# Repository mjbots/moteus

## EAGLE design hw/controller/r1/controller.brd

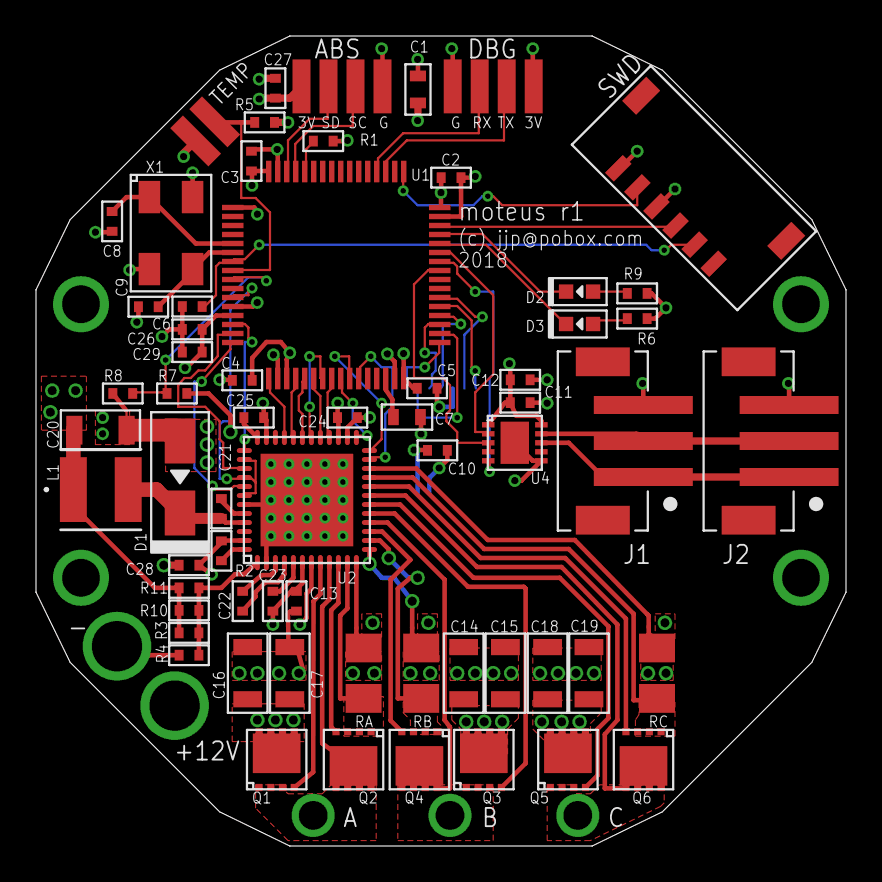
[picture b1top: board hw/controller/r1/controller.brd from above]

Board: 4 copper layers, 45.0 x 45.0 mm, 77 parts (1 on the bottom side), 68 nets.

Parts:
A: PAD; 18AWG_PAD
ABS: PAD4; PAD15_4
B: PAD; 18AWG_PAD
C: PAD; 18AWG_PAD
C1, C7: 4.7uF; C0603
C2, C3, C4, C5, C6, C10, C11, C13, C21, C22, C26: 0.1uF 50V; C0402
C8, C9: 10pF; C0402
C12, C23, C24, C25, C27, C28, C29: 1uF 35V; C0402
C14, C15, C16, C17, C18, C19, C20: 15uF; C1206
D1: MF-DIO-SMA-B140; SMA
D2, D3: MF-LED-0603-RED; LED0603
DBG: PAD4; PAD15_4
J1, J2: JST-PH3SMT_VERT; JST_B3B_PH-SM4-TB(LF)(SN)
L1: SRN4018-220M; IND_BOURNS_SRN4018
Q1, Q2, Q3, Q4, Q5, Q6: TPN1R603PL; TSON_ADVANCE_8
R1, R6, R9: 220; R0402
R2, R3, R7, R10, R11: 100k 1%; R0402
R4, R5, R8: 10k 1%; R0402
RA: 1mOhm 1% 2W; M1206
RB: 1mOhm 1% 2W; M1206
RC: 1mOhm 1% 2W; M1206
SH1, SH2, SH3: SHORTT5; SHORT_TOP-50
SH4: SHORTBIG; SHORT_TOP-BIG
SWD: JST-ZH6; JST_S6B-ZR-SM4A-TF(LF)(SN)
TEMP: PAD2; PAD15_2
U1: STM32F4R_64PIN; LQFP64
U2: DRV8323RS; PVQFN-N48
U3: AS5147; TSSOP14
U4: MAX13431E; TDFN10
U$1, U$2, U$3, U$4: MOUNTM2; M2MOUNT
V+: PAD12AWG_PAD; 12AWG_PAD
V-: PAD12AWG_PAD; 12AWG_PAD
X1: 8.0MHz; ABM3B

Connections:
+3V3: ABS.1, C1.P$1, C2.P$1, C3.P$1, C4.P$1, C5.P$1, C10.P$1, C11.P$1, C12.P$1, C20.P$1, C24.P$2, C26.P$1, C27.P$1, C29.P$1, DBG.1, L1.1, R3.P$1, R6.P$1, R9.P$1, R10.P$1, R11.P$1, SWD.6, TEMP.1, U1.1, U1.13, U1.19, U1.32, U1.48, U1.64, U2.26, U3.12, U4.1, U4.10
AS5047_A: U1.37, U3.7
AS5047_B: U1.38, U3.6
AS5047_CS: U1.33, U3.1
AS5047_MISO: U1.35, U3.3
AS5047_MOSI: U1.36, U3.4
AS5047_SCK: U1.34, U3.2
CUR1: U1.25, U2.25
CUR2: U1.26, U2.24
CUR3: U1.27, U2.23
DEBUG_RX: DBG.3, U1.52
DEBUG_TX: DBG.2, U1.51
DRV8323_CS: U1.20, U2.32
DRV8323_MISO: U1.22, U2.29
DRV8323_MOSI: U1.23, U2.30
DRV8323_SCLK: U1.21, U2.31
GHA: Q1.4, U2.8
GHB: Q3.4, U2.17
GHC: Q5.4, U2.18
GLA: Q2.4, U2.10
GLB: Q4.4, U2.15
GLC: Q6.4, U2.20
GND: ABS.4, C1.P$2, C2.P$2, C3.P$2, C4.P$2, C5.P$2, C6.P$2, C7.P$2, C8.P$2, C9.P$2, C10.P$2, C11.P$2, C12.P$2, C20.P$2, C24.P$1, C25.P$1, C26.P$2, C27.P$2, C29.P$2, DBG.4, J1.3, J2.3, R1.P$1, R5.P$2, R8.P$1, SH4.2, SWD.4, U1.12, U1.18, U1.31, U1.47, U1.63, U2.27, U2.35, U3.5, U3.13, U4.6, U4.PAD, X1.2, X1.4
I2C_ABS_SCL: ABS.3, U1.61
I2C_ABS_SDA: ABS.2, U1.62
LED1: D3.CATHODE, U1.44
LED2: D2.CATHODE, U1.45
MOTOR1: U1.14, U2.37
MOTOR2: U1.15, U2.39
MOTOR3: U1.16, U2.41
MOTOR_ENABLE: U1.17, U2.33
MOTOR_FAULT: U1.24, U2.28
MOTOR_HIZ: U1.11, U2.38, U2.40, U2.42
unnamed: R2.P$1, U2.48
unnamed: SWD.5, U1.49
unnamed: SWD.3, U1.46
unnamed: R3.P$2, R4.P$1, R10.P$2, R11.P$2, U2.1
unnamed: J1.2, J2.2, U4.9
unnamed: C22.P$2, U2.3
unnamed: C21.P$2, D1.CATHODE, L1.2, U2.45
unnamed: C21.P$1, U2.44
unnamed: C22.P$1, U2.4
unnamed: C23.P$2, U2.5
unnamed: J1.1, J2.1, U4.8
unnamed: C25.P$2, U2.36
unnamed: D3.ANODE, R6.P$2
unnamed: D2.ANODE, R9.P$2
unnamed: C7.P$1, U1.30
unnamed: C6.P$1, SWD.2, U1.7
unnamed: R1.P$2, U1.60
unnamed: C8.P$1, U1.5, X1.1
unnamed: C9.P$1, U1.6, X1.3
RS485_DIR: U1.41, U4.3, U4.4
RS485_RX: U1.43, U4.2
RS485_TX: U1.42, U4.5
SHA: A.1, Q1.1, Q1.2, Q1.3, Q2.5, Q2.6, Q2.7, Q2.8, Q2.PAD, U2.9
SHB: B.1, Q3.1, Q3.2, Q3.3, Q4.5, Q4.6, Q4.7, Q4.8, Q4.PAD, U2.16
SHC: C.1, Q5.1, Q5.2, Q5.3, Q6.5, Q6.6, Q6.7, Q6.8, Q6.PAD, U2.19
SNA: SH1.1, U2.12
SNB: SH2.1, U2.13
SNC: SH3.1, U2.22
SPA: Q2.1, Q2.2, Q2.3, RA.2, U2.11
SPB: Q4.1, Q4.2, Q4.3, RB.2, U2.14
SPC: Q6.1, Q6.2, Q6.3, RC.2, U2.21
V+: C13.P$1, C14.P$1, C15.P$1, C16.P$1, C17.P$1, C18.P$1, C19.P$1, C23.P$1, C28.P$1, Q1.5, Q1.6, Q1.7, Q1.8, Q1.PAD, Q3.5, Q3.6, Q3.7, Q3.8, Q3.PAD, Q5.5, Q5.6, Q5.7, Q5.8, Q5.PAD, R2.P$2, R7.P$2, U2.6, U2.7, U2.47, V+.1
V-: C13.P$2, C14.P$2, C15.P$2, C16.P$2, C17.P$2, C18.P$2, C19.P$2, C28.P$2, D1.ANODE, R4.P$2, RA.1, RB.1, RC.1, SH1.2, SH2.2, SH3.2, SH4.1, U2.2, U2.43, U2.P1, U2.P2, U2.P3, U2.P4, U2.P5, U2.P6, U2.P7, U2.P8, U2.P9, U2.P10, U2.P11, U2.P12, U2.P13, U2.P14, U2.P15, U2.P16, U2.P17, U2.P18, U2.P19, U2.P20, U2.P21, U2.P22, U2.P23, U2.P24, U2.P25, U2.PAD, V-.1
VBAT_SENSE: R7.P$1, R8.P$2, U1.9
VTEMP: R5.P$1, TEMP.2, U1.8

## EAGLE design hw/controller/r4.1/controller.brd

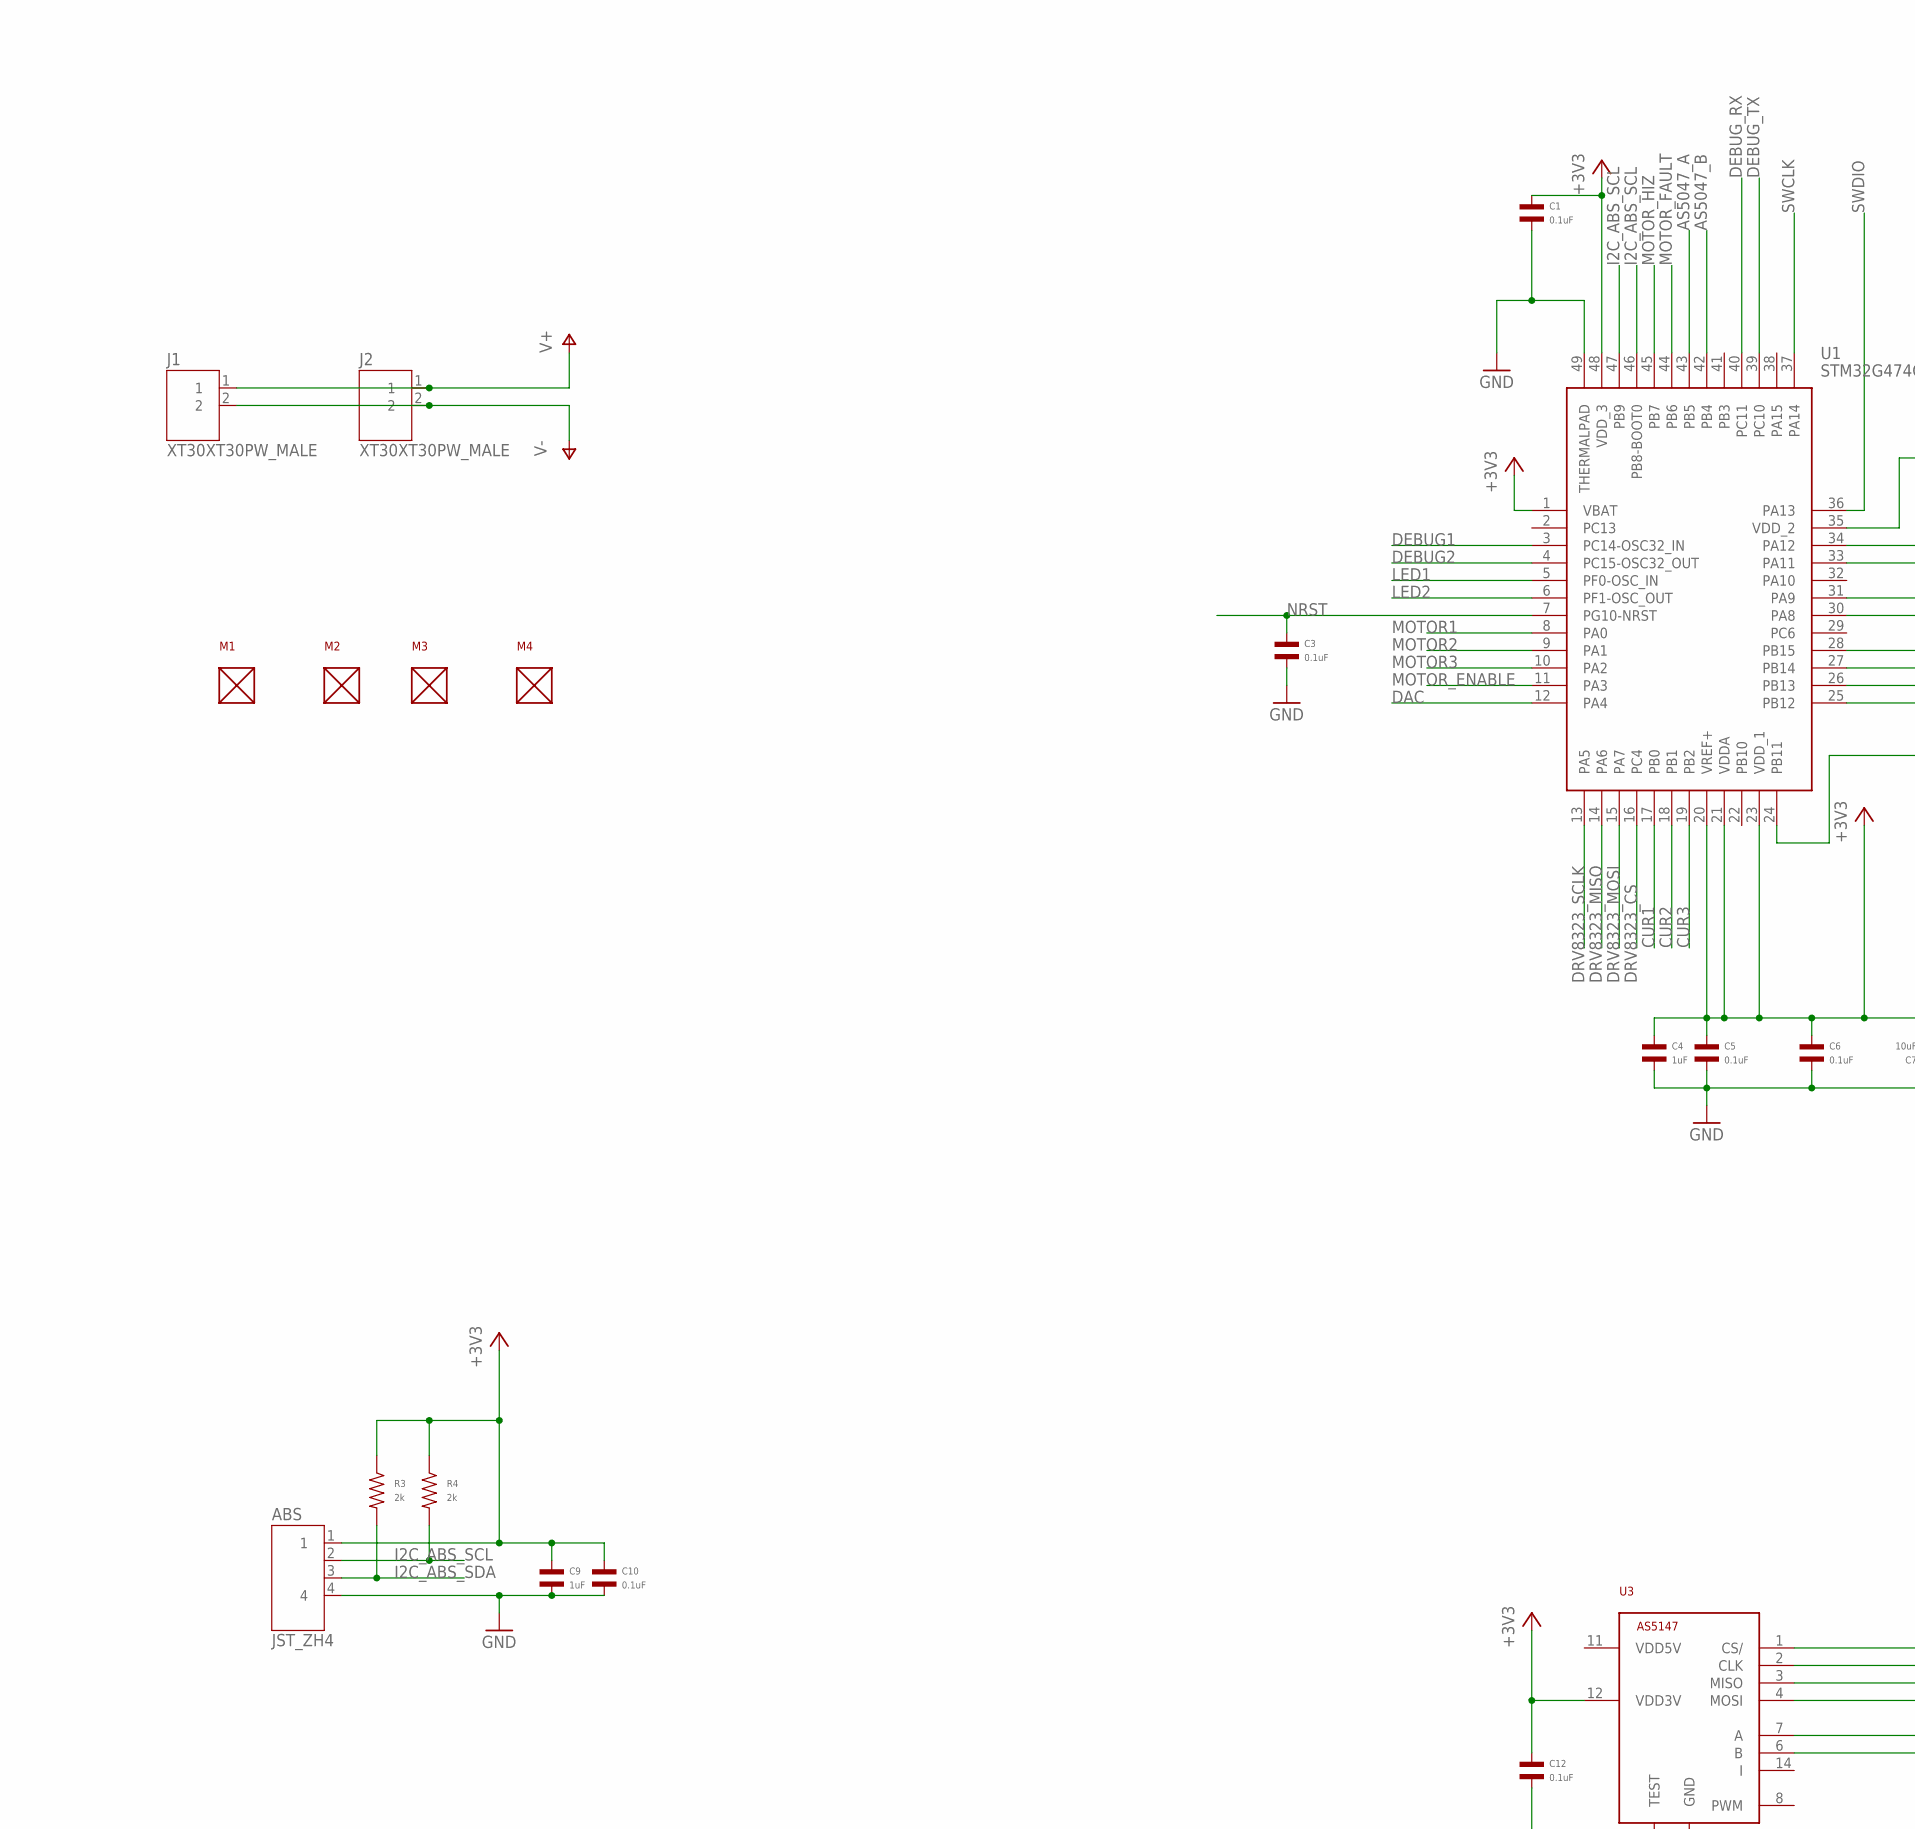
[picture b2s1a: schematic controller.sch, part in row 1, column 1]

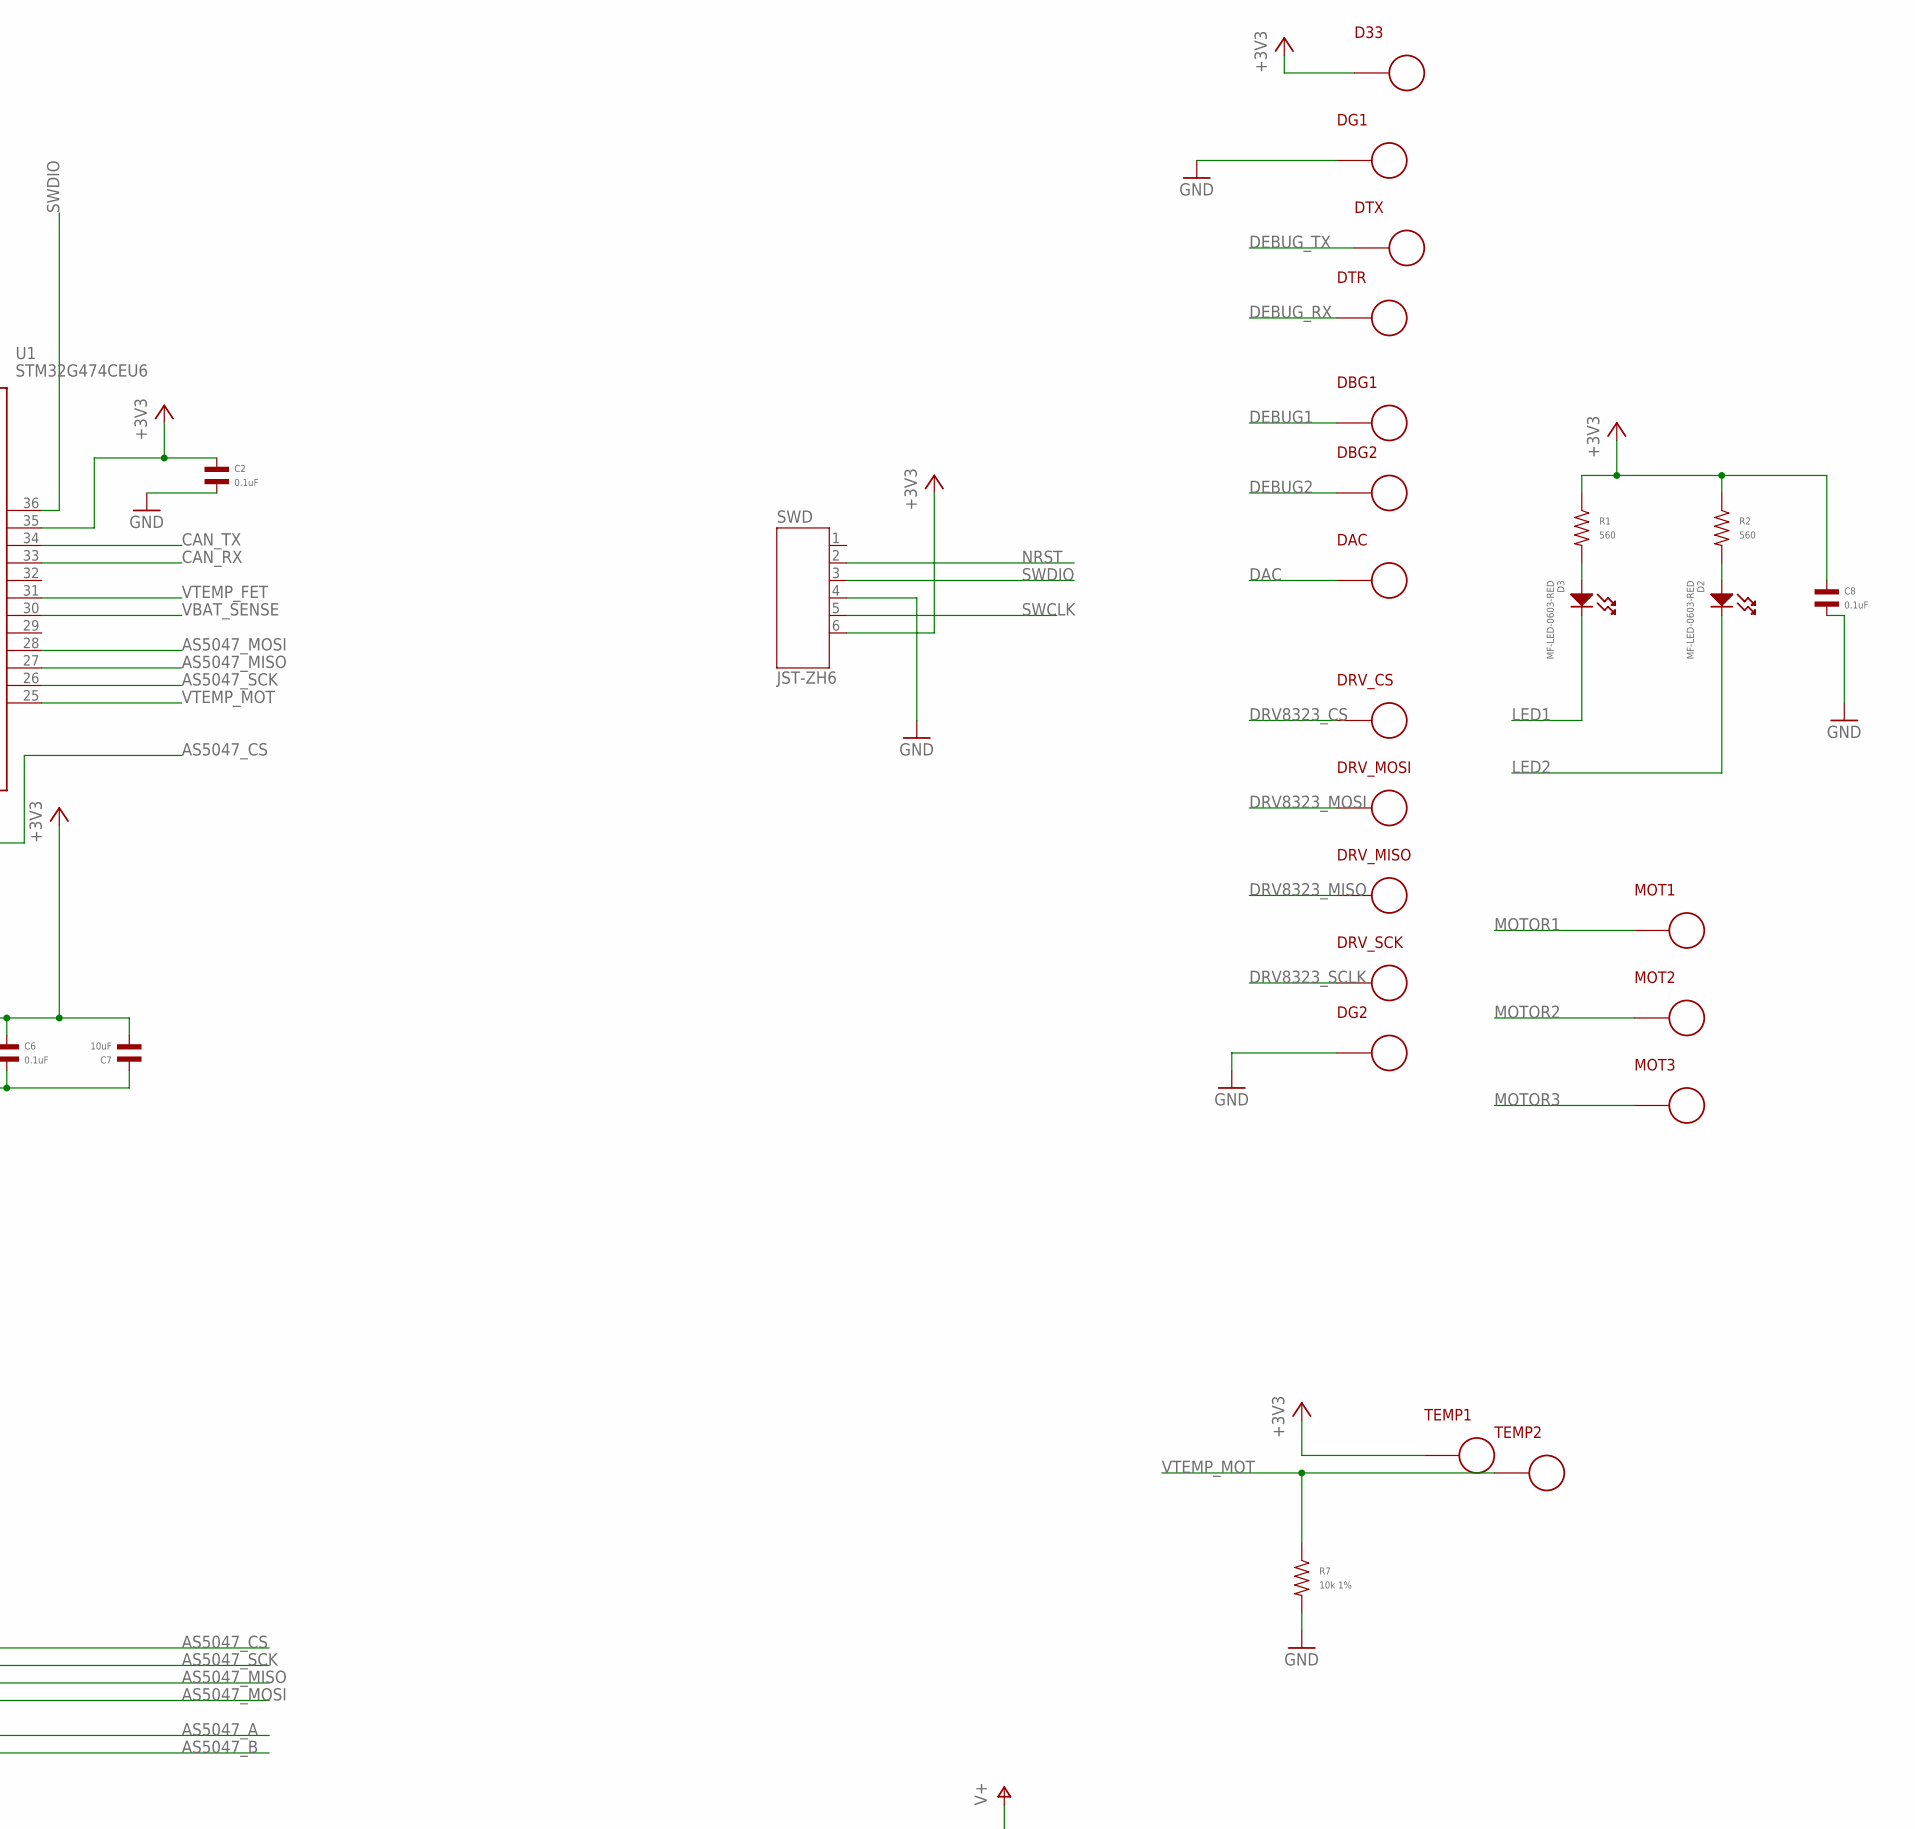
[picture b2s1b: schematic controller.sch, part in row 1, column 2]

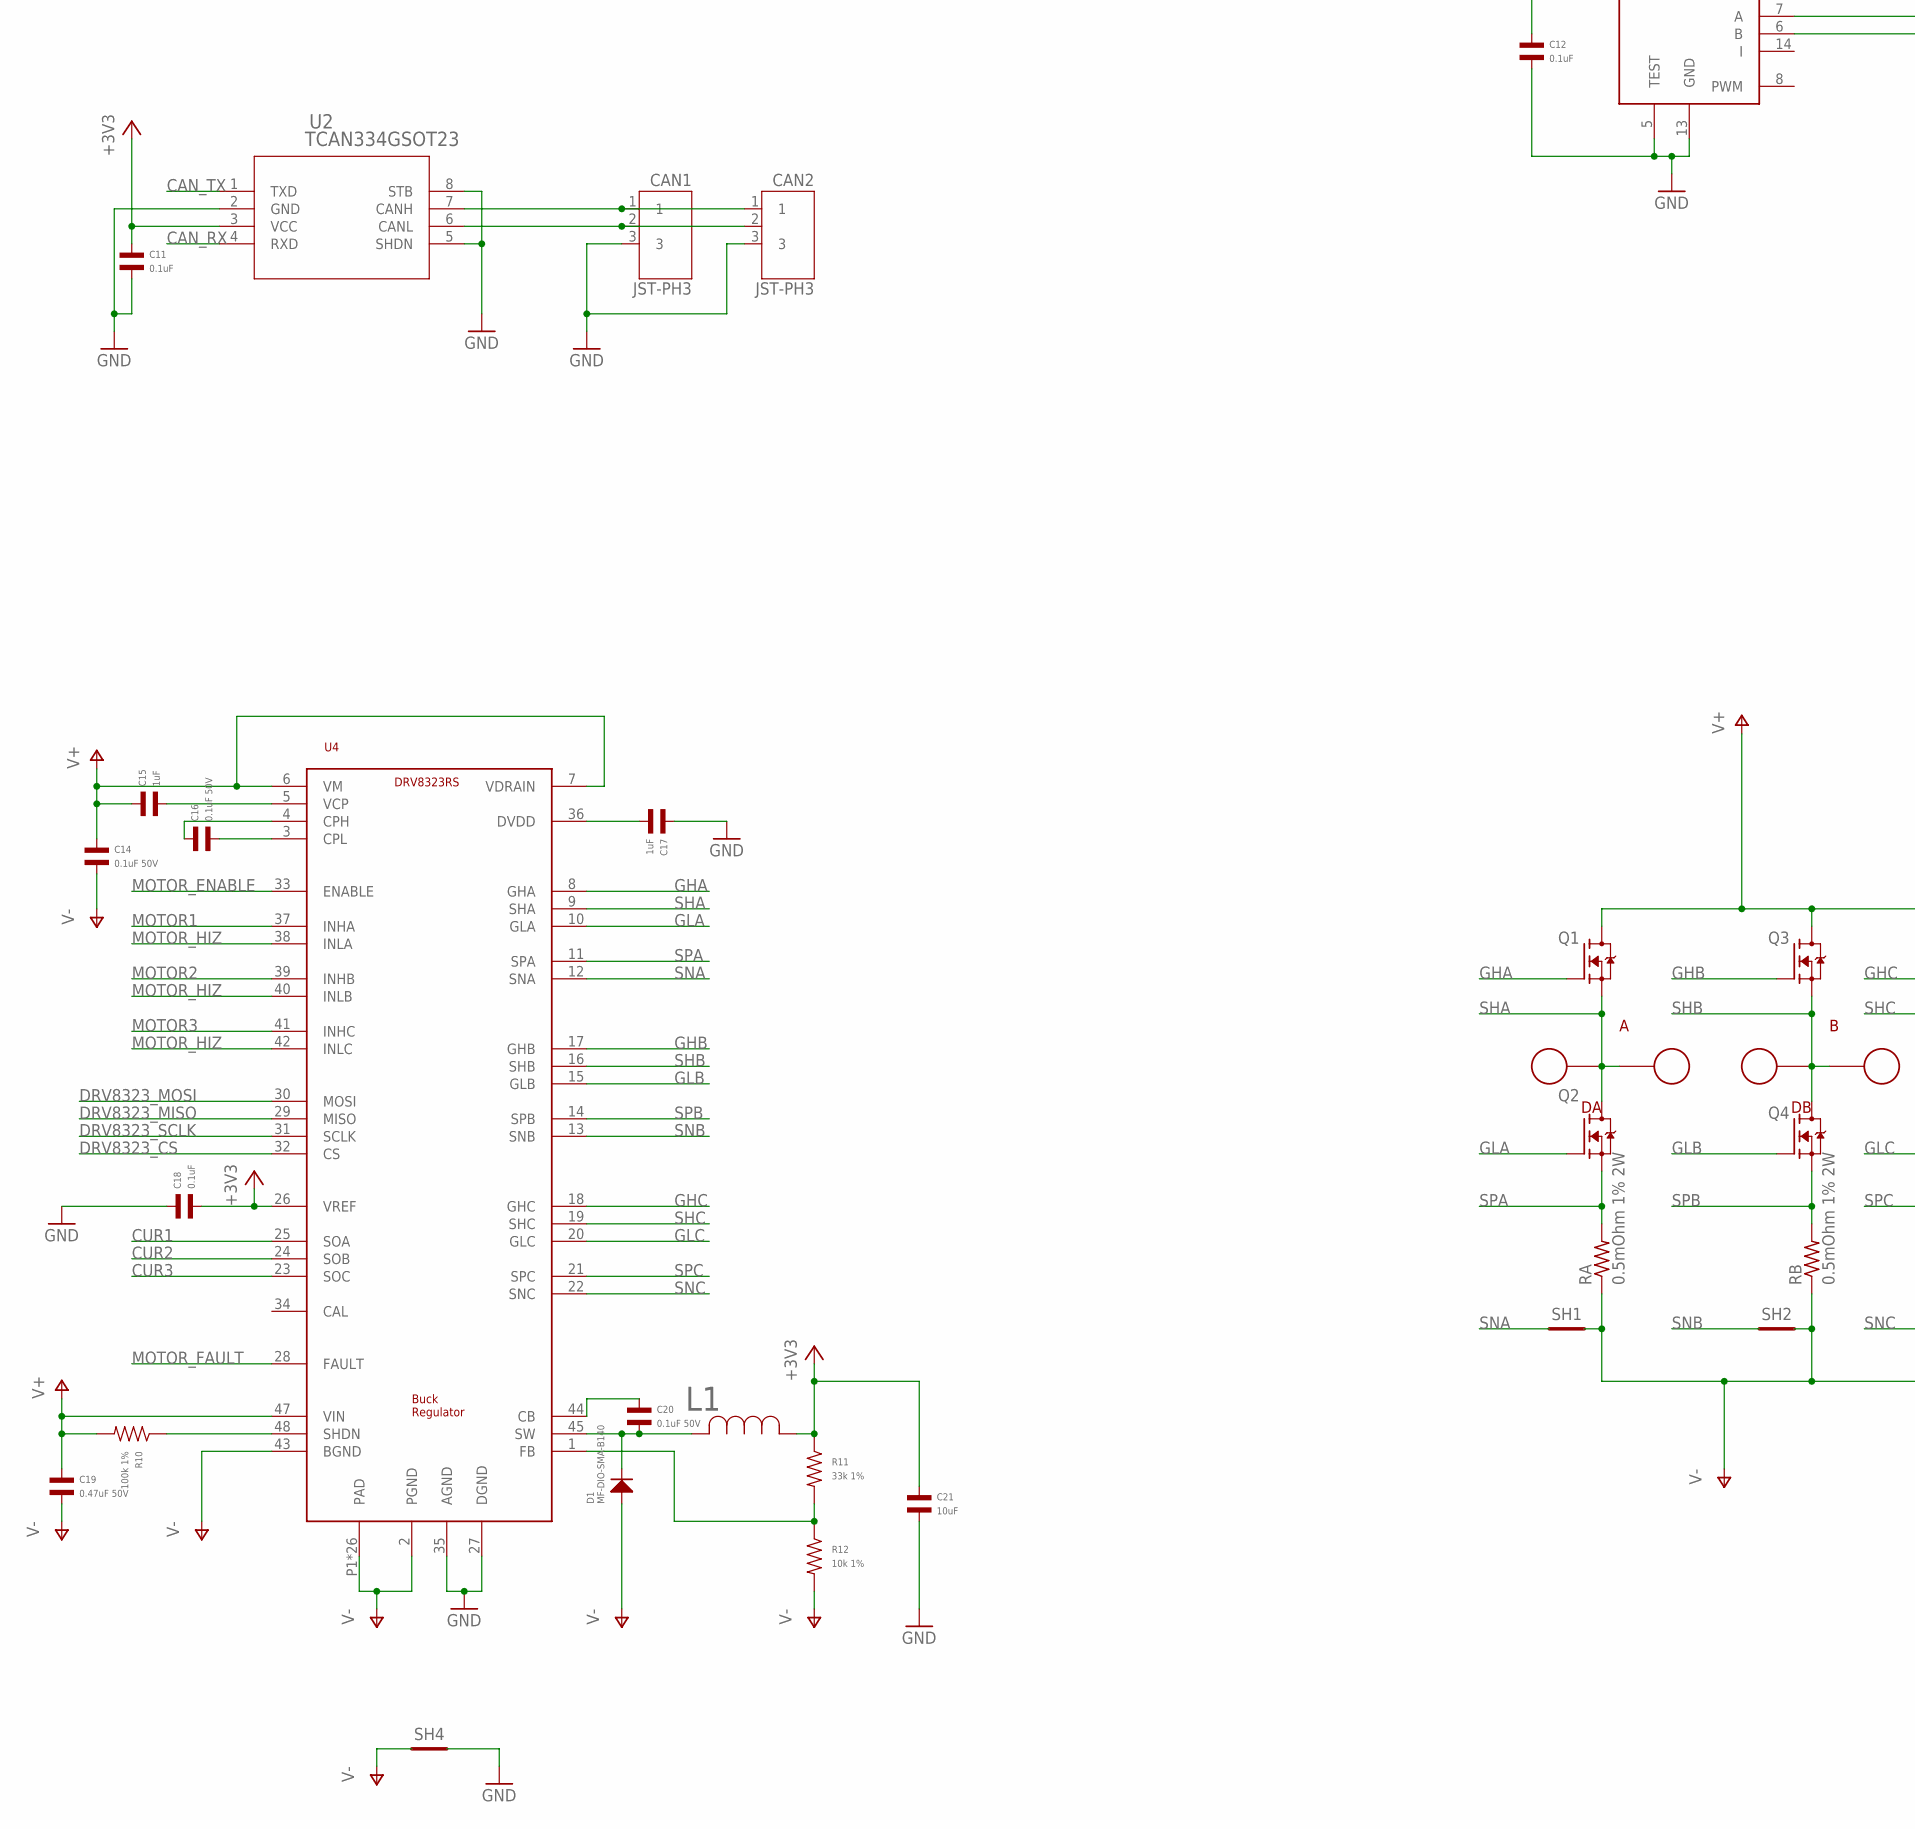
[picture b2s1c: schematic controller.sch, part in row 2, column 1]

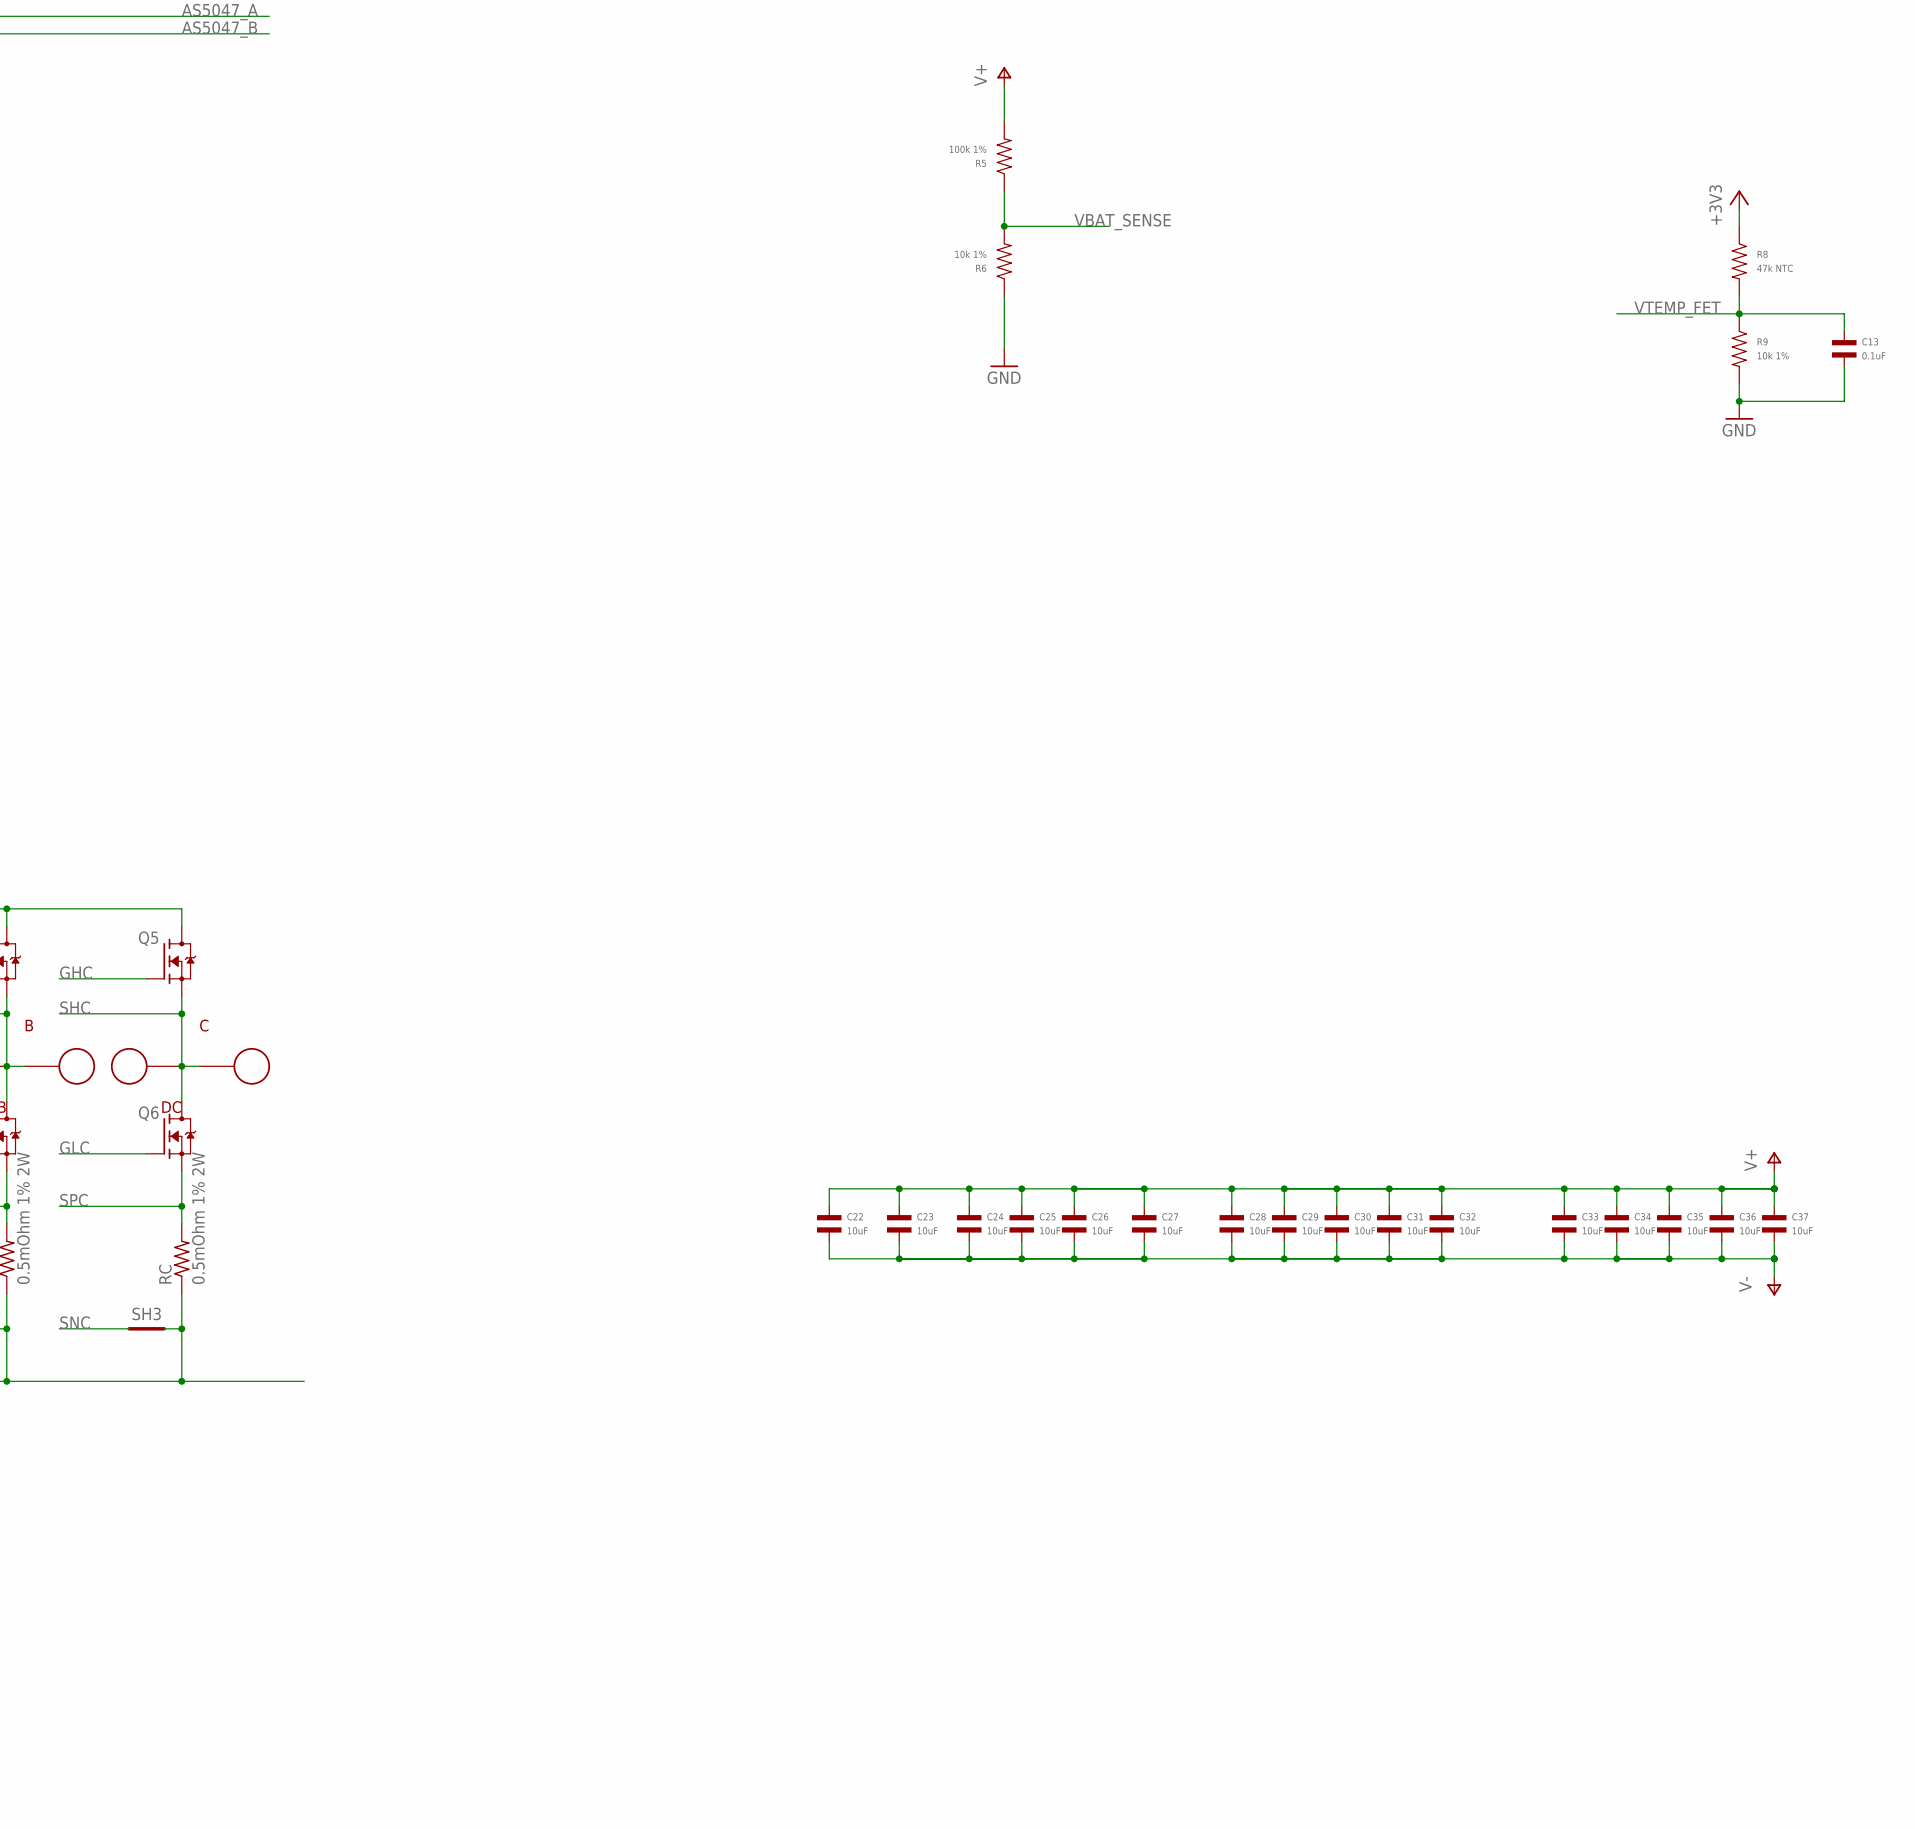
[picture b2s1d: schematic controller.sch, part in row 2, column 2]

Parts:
A: PAD; 18AWG_PAD
ABS: JST_ZH4; JST_S4B-ZR-SM4A-TF(LF)(SN); MPN S4B-ZR-SM4A-TF(LF)(SN)
B: PAD; 18AWG_PAD
C: PAD; 18AWG_PAD
C1, C2, C3, C5, C6, C8, C10, C11, C12, C13, C18: 0.1uF; C0402; MPN MF-CAP-0402-0.1uF
C4, C9, C15, C17: 1uF; C0402; MPN MF-CAP-0402-1uF
C7, C21: 10uF; C1206; MPN MF-CAP-1206-10uF
C14, C16, C20: 0.1uF 50V; C0402; MPN CGA2B3X7R1H104K050BB
C19: 0.47uF 50V; C0402; MPN UMK105ABJ474KV-F
C22, C23, C24, C25, C26, C27, C28, C29, C30, C31, C32, C33, C34, C35, C36, C37: 10uF; C1206; MPN CGA5L1X7R1H106K160AC
CAN1, CAN2: JST-PH3; JST_S3B-PH-SM4-TB(LF)(SN); MPN S3B-PH-SM4-TB(LF)(SN)
D1: MF-DIO-SMA-B140; SMA
D2: MF-LED-0603-RED; LED0603; MPN MF-LED-0603-GREEN
D3: MF-LED-0603-RED; LED0603
D33: PAD24AWG_PAD; 24AWG_PAD
DA: PAD24AWG_PAD; 24AWG_PAD
DAC: PAD24AWG_PAD; 24AWG_PAD
DB: PAD24AWG_PAD; 24AWG_PAD
DBG1, DBG2: PAD24AWG_PAD; 24AWG_PAD
DC: PAD24AWG_PAD; 24AWG_PAD
DG1, DG2: PAD24AWG_PAD; 24AWG_PAD
DRV_CS: PAD24AWG_PAD; 24AWG_PAD
DRV_MISO: PAD24AWG_PAD; 24AWG_PAD
DRV_MOSI: PAD24AWG_PAD; 24AWG_PAD
DRV_SCK: PAD24AWG_PAD; 24AWG_PAD
DTR: PAD24AWG_PAD; 24AWG_PAD
DTX: PAD24AWG_PAD; 24AWG_PAD
J1, J2: XT30XT30PW_MALE; XT30PW_MALE
L1: SRN4018-220M; IND_BOURNS_SRN4018; MPN SRN4018-220M
M1, M2, M3, M4: MOUNT; M2.5MOUNT
MOT1, MOT2, MOT3: PAD24AWG_PAD; 24AWG_PAD
Q1, Q2, Q3, Q4, Q5, Q6: TPH1R204PLSOP_ADVANCE_8; SOP_ADVANCE_8; MPN TPH1R204PL,L1Q
R1, R2: 560; R0402; MPN MF-RES-0402-560
R3, R4: 2k; R0402; MPN MF-RES-0402-2K
R5, R10: 100k 1%; R0402; MPN ERJ-2RKF1003X
R6, R7, R9, R12: 10k 1%; R0402; MPN ERJ-2RKF1002X
R8: 47k NTC; R0402; MPN NCP15WB473F03RC
R11: 33k 1%; R0402; MPN ERJ-2RKF3302X
RA: 0.5mOhm 1% 2W; M1206; MPN HCS1206FTL500
RB: 0.5mOhm 1% 2W; M1206; MPN HCS1206FTL500
RC: 0.5mOhm 1% 2W; M1206; MPN HCS1206FTL500
SH1, SH2, SH3: SHORTT5; SHORT_TOP-50
SH4: SHORTBIG; SHORT_TOP-BIG
SWD: JST-ZH6; JST_S6B-ZR-SM4A-TF(LF)(SN); MPN S6B-ZR-SM4A-TF(LF)(SN)
TEMP1, TEMP2: PAD24AWG_PAD; 24AWG_PAD
U1: STM32G474CEU6; QFN50P700X700X60-49N; MPN STM32G474CEU6
U2: TCAN334GSOT23; SOT23-8; MPN TCAN334GDCNT
U3: AS5147; TSSOP14; MPN AS5047P-ATSM
U4: DRV8323RS; PVQFN-N48; MPN DRV8323RSRGZR

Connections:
+3V3: ABS.1, C1.P$1, C2.P$1, C4.P$1, C5.P$1, C6.P$1, C7.P$2, C8.P$1, C9.P$1, C10.P$1, C11.P$1, C12.P$1, C18.P$2, C21.P$1, D33.P$1, L1.1, R1.P$1, R2.P$1, R3.P$1, R4.P$1, R8.P$1, R11.P$1, SWD.6, TEMP1.P$1, U1.1 (VBAT), U1.20 (VREF+), U1.21 (VDDA), U1.23 (VDD_1), U1.35 (VDD_2), U1.48 (VDD_3), U2.3 (VCC), U3.12 (VDD3V), U4.26 (VREF)
AS5047_A: U1.43 (PB5), U3.7 (A)
AS5047_B: U1.42 (PB4), U3.6 (B)
AS5047_CS: U1.24 (PB11), U3.1 (CS/)
AS5047_MISO: U1.27 (PB14), U3.3 (MISO)
AS5047_MOSI: U1.28 (PB15), U3.4 (MOSI)
AS5047_SCK: U1.26 (PB13), U3.2 (CLK)
CAN_N: CAN1.2, CAN2.2, U2.6 (CANL)
CAN_P: CAN1.1, CAN2.1, U2.7 (CANH)
CAN_RX: U1.33 (PA11), U2.4 (RXD)
CAN_TX: U1.34 (PA12), U2.1 (TXD)
CUR1: U1.17 (PB0), U4.25 (SOA)
CUR2: U1.18 (PB1), U4.24 (SOB)
CUR3: U1.19 (PB2), U4.23 (SOC)
DAC: DAC.P$1, U1.12 (PA4)
DEBUG1: DBG1.P$1, U1.3 (PC14-OSC32_IN)
DEBUG2: DBG2.P$1, U1.4 (PC15-OSC32_OUT)
DEBUG_RX: DTR.P$1, U1.40 (PC11)
DEBUG_TX: DTX.P$1, U1.39 (PC10)
DRV8323_CS: DRV_CS.P$1, U1.16 (PC4), U4.32 (CS)
DRV8323_MISO: DRV_MISO.P$1, U1.14 (PA6), U4.29 (MISO)
DRV8323_MOSI: DRV_MOSI.P$1, U1.15 (PA7), U4.30 (MOSI)
DRV8323_SCLK: DRV_SCK.P$1, U1.13 (PA5), U4.31 (SCLK)
GHA: Q1.4 (G), U4.8 (GHA)
GHB: Q3.4 (G), U4.17 (GHB)
GHC: Q5.4 (G), U4.18 (GHC)
GLA: Q2.4 (G), U4.10 (GLA)
GLB: Q4.4 (G), U4.15 (GLB)
GLC: Q6.4 (G), U4.20 (GLC)
GND: ABS.4, C1.P$2, C2.P$2, C3.P$2, C4.P$2, C5.P$2, C6.P$2, C7.P$1, C8.P$2, C9.P$2, C10.P$2, C11.P$2, C12.P$2, C13.P$2, C17.P$1, C18.P$1, C21.P$2, CAN1.3, CAN2.3, DG1.P$1, DG2.P$1, R6.P$1, R7.P$2, R9.P$2, SH4.2, SWD.4, U1.49 (THERMALPAD), U2.2 (GND), U2.5 (SHDN), U2.8 (STB), U3.5 (TEST), U3.13 (GND), U4.27 (DGND), U4.35 (AGND)
I2C_ABS_SCL: ABS.2, R4.P$2, U1.46 (PB8-BOOT0), U1.47 (PB9)
I2C_ABS_SDA: ABS.3, R3.P$2
LED1: D3.CATHODE, U1.5 (PF0-OSC_IN)
LED2: D2.CATHODE, U1.6 (PF1-OSC_OUT)
MOTOR1: MOT1.P$1, U1.8 (PA0), U4.37 (INHA)
MOTOR2: MOT2.P$1, U1.9 (PA1), U4.39 (INHB)
MOTOR3: MOT3.P$1, U1.10 (PA2), U4.41 (INHC)
MOTOR_ENABLE: U1.11 (PA3), U4.33 (ENABLE)
MOTOR_FAULT: U1.44 (PB6), U4.28 (FAULT)
MOTOR_HIZ: U1.45 (PB7), U4.38 (INLA), U4.40 (INLB), U4.42 (INLC)
unnamed: R10.P$1, U4.48 (SHDN)
unnamed: R11.P$2, R12.P$1, U4.1 (FB)
unnamed: C16.P$2, U4.3 (CPL)
unnamed: C20.P$2, D1.CATHODE, L1.2, U4.45 (SW)
unnamed: C20.P$1, U4.44 (CB)
unnamed: C16.P$1, U4.4 (CPH)
unnamed: C15.P$2, U4.5 (VCP)
unnamed: C17.P$2, U4.36 (DVDD)
unnamed: D3.ANODE, R1.P$2
unnamed: D2.ANODE, R2.P$2
NRST: C3.P$1, SWD.2, U1.7 (PG10-NRST)
SHA: A.1, DA.P$1, Q1.1 (S), Q1.2 (S), Q1.3 (S), Q2.5 (D), Q2.6 (D), Q2.7 (D), Q2.8 (D), Q2.PAD (D), U4.9 (SHA)
SHB: B.1, DB.P$1, Q3.1 (S), Q3.2 (S), Q3.3 (S), Q4.5 (D), Q4.6 (D), Q4.7 (D), Q4.8 (D), Q4.PAD (D), U4.16 (SHB)
SHC: C.1, DC.P$1, Q5.1 (S), Q5.2 (S), Q5.3 (S), Q6.5 (D), Q6.6 (D), Q6.7 (D), Q6.8 (D), Q6.PAD (D), U4.19 (SHC)
SNA: SH1.1, U4.12 (SNA)
SNB: SH2.1, U4.13 (SNB)
SNC: SH3.1, U4.22 (SNC)
SPA: Q2.1 (S), Q2.2 (S), Q2.3 (S), RA.2, U4.11 (SPA)
SPB: Q4.1 (S), Q4.2 (S), Q4.3 (S), RB.2, U4.14 (SPB)
SPC: Q6.1 (S), Q6.2 (S), Q6.3 (S), RC.2, U4.21 (SPC)
SWCLK: SWD.5, U1.37 (PA14)
SWDIO: SWD.3, U1.36 (PA13)
V+: C14.P$1, C15.P$1, C19.P$1, C22.P$1, C23.P$1, C24.P$1, C25.P$1, C26.P$1, C27.P$1, C28.P$1, C29.P$1, C30.P$1, C31.P$1, C32.P$1, C33.P$1, C34.P$1, C35.P$1, C36.P$1, C37.P$1, J1.1, J2.1, Q1.5 (D), Q1.6 (D), Q1.7 (D), Q1.8 (D), Q1.PAD (D), Q3.5 (D), Q3.6 (D), Q3.7 (D), Q3.8 (D), Q3.PAD (D), Q5.5 (D), Q5.6 (D), Q5.7 (D), Q5.8 (D), Q5.PAD (D), R5.P$2, R10.P$2, U4.6 (VM), U4.7 (VDRAIN), U4.47 (VIN)
V-: C14.P$2, C19.P$2, C22.P$2, C23.P$2, C24.P$2, C25.P$2, C26.P$2, C27.P$2, C28.P$2, C29.P$2, C30.P$2, C31.P$2, C32.P$2, C33.P$2, C34.P$2, C35.P$2, C36.P$2, C37.P$2, D1.ANODE, J1.2, J2.2, R12.P$2, RA.1, RB.1, RC.1, SH1.2, SH2.2, SH3.2, SH4.1, U4.2 (PGND), U4.43 (BGND), U4.P1 (PAD), U4.P2 (PAD), U4.P3 (PAD), U4.P4 (PAD), U4.P5 (PAD), U4.P6 (PAD), U4.P7 (PAD), U4.P8 (PAD), U4.P9 (PAD), U4.P10 (PAD), U4.P11 (PAD), U4.P12 (PAD), U4.P13 (PAD), U4.P14 (PAD), U4.P15 (PAD), U4.P16 (PAD), U4.P17 (PAD), U4.P18 (PAD), U4.P19 (PAD), U4.P20 (PAD), U4.P21 (PAD), U4.P22 (PAD), U4.P23 (PAD), U4.P24 (PAD), U4.P25 (PAD), U4.PAD
VBAT_SENSE: R5.P$1, R6.P$2, U1.30 (PA8)
VTEMP_FET: C13.P$1, R8.P$2, R9.P$1, U1.31 (PA9)
VTEMP_MOT: R7.P$1, TEMP2.P$1, U1.25 (PB12)

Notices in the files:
hw/controller/r4.1/controller.sch:
Licensed under the Apache 2.0 License
hw/controller/r4.6/controller.brd:
(c) 2021
hw/n1/r1/moteus_n1.brd:
(c) 2022
parts and their libraries:
power_dist: COPYRIGHT: Copyright (C) 2018 Accelerated Designs. All rights reserved
COPYRIGHT: Copyright (C) 2022 Ultra Librarian. All rights reserved.
